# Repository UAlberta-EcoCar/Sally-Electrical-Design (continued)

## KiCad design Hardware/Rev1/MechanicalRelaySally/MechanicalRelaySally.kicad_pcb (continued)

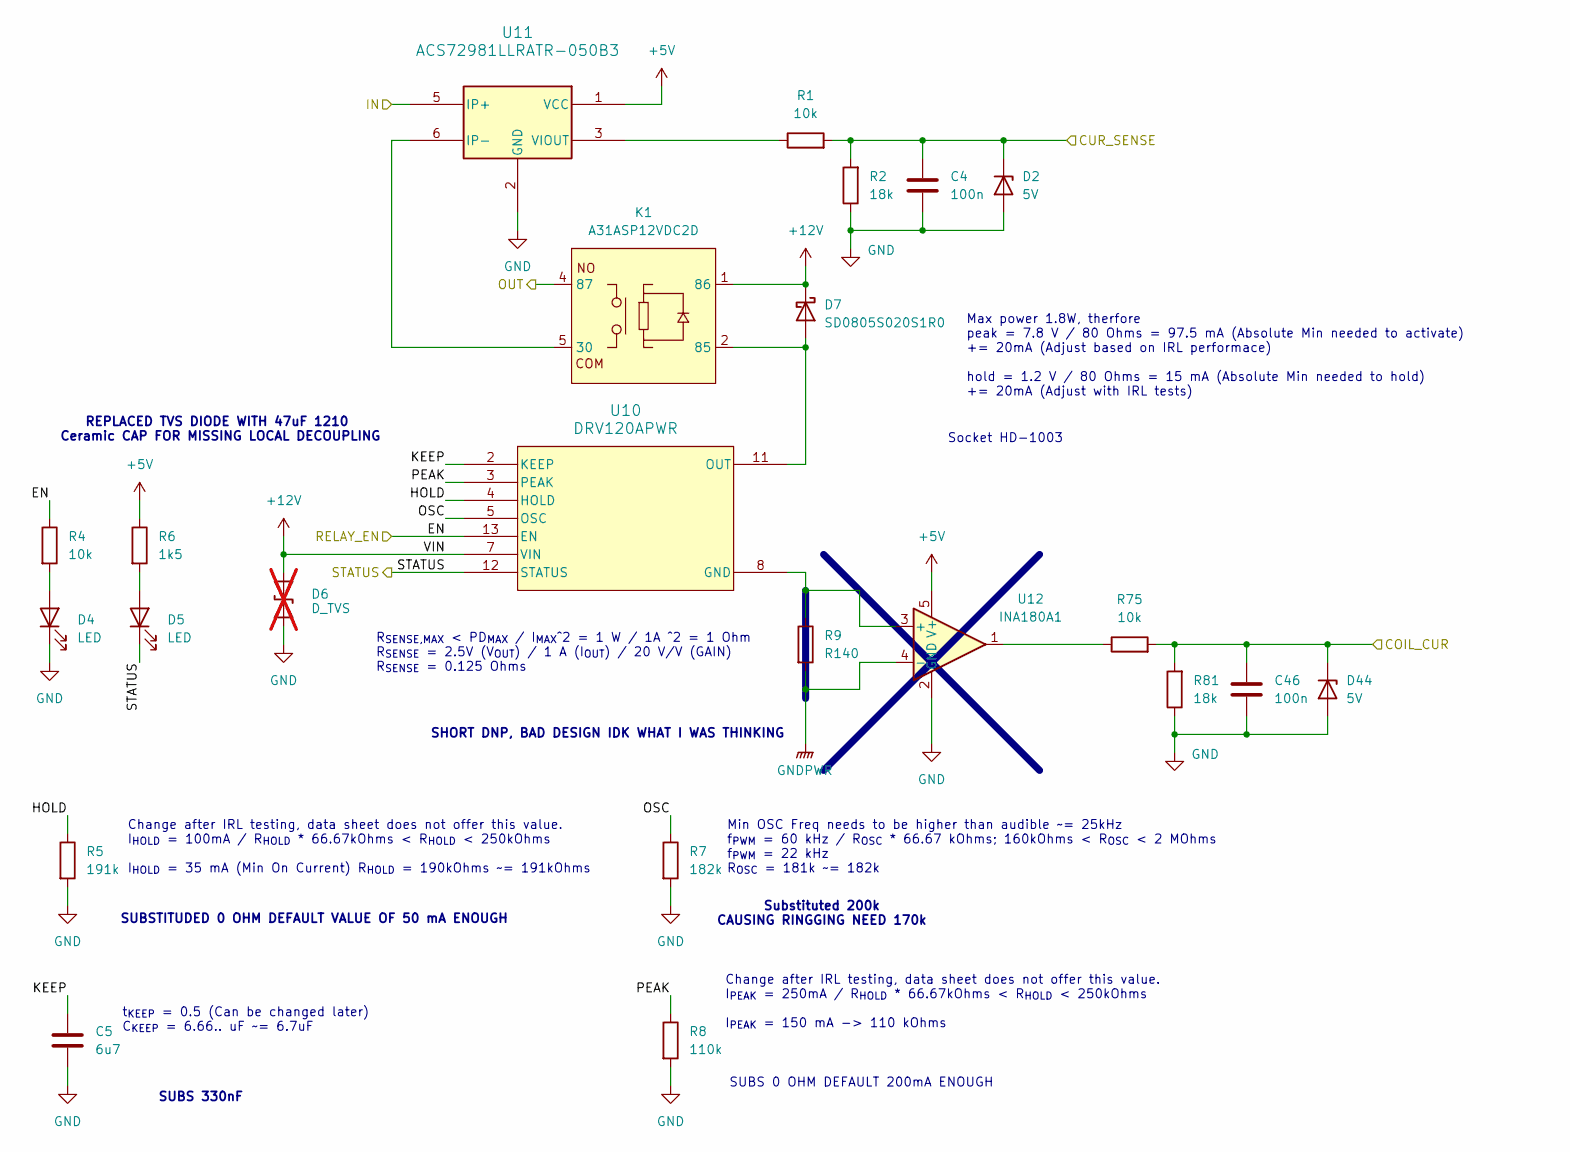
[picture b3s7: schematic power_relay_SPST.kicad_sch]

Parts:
C4, C46: 100n; C_0402_1005Metric
C5: 6u7; C_0603_1608Metric
D2, D44: 5V; D_SOD-323F
D4, D5: LED; LED_0603_1608Metric
D6: D_TVS; D_SOD_123_M; not fitted
D7: SD0805S020S1R0; D_SOD-123; Part# 478-7800-1-ND
K1: A31ASP12VDC2D; A3_HeavyDuty_PCPIN; Part# 2449-A31ASP12VDC2D-ND
R1, R4, R75: 10k; R_0603_1608Metric
R2, R81: 18k; R_0603_1608Metric
R5: 191k; R_0603_1608Metric
R6: 1k5; R_0603_1608Metric
R7: 182k; R_0603_1608Metric
R8: 110k; R_0603_1608Metric
R9: R140; R_1206_3216Metric
U10: DRV120APWR; PW14_TEX
U11: ACS72981LLRATR-050B3; XDCR_ACS72981LLRATR-100B5
U12: INA180A1; SOT-23-5

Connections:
+5V: R6.1, U11.1 (VCC), U12.5 (V+); also elsewhere on the board
+12V: D6.2 (A2), D7.1 (K), K1.1 (86), U10.7 (VIN); also elsewhere on the board
/Microcontroller/MTR_RLY.COIL_CUR: C46.1, D44.1 (K), R75.2, R81.2; also elsewhere on the board
/Microcontroller/MTR_RLY.CUR_SENSE: C4.1, D2.1 (K), R1.2, R2.2; also elsewhere on the board
/Microcontroller/MTR_RLY.RELAY_EN: R4.1, U10.13 (EN); also elsewhere on the board
/Microcontroller/MTR_RLY.STATUS: D5.1 (K), U10.12 (STATUS); also elsewhere on the board
/Power Routing/MOTOR Power Relay1/HOLD: R5.1, U10.4 (HOLD)
/Power Routing/MOTOR Power Relay1/KEEP: C5.1, U10.2 (KEEP)
/Power Routing/MOTOR Power Relay1/OSC: R7.1, U10.5 (OSC)
/Power Routing/MOTOR Power Relay1/PEAK: R8.1, U10.3 (PEAK)
/Power Routing/VOLT_MEAS.FC_OUT: U11.5 (IP+); also elsewhere on the board
/Power Routing/VOLT_MEAS.MTR_OUT: K1.4 (87); also elsewhere on the board
GND: C4.2, C5.2, C46.2, D2.2 (A), D4.1 (K), D6.1 (A1), D44.2 (A), R2.1, R5.2, R7.2, R8.2, R9.2, R81.1, U11.2 (GND), U11.4 (NC), U12.2 (GND), U12.4 (-); also elsewhere on the board
unnamed: D4.2 (A), R4.2
unnamed: D5.2 (A), R6.2
unnamed: D7.2 (A), K1.2 (85), U10.11 (OUT)
unnamed: K1.5 (30), U11.6 (IP-)
unnamed: R75.1, U12.1
unnamed: R9.1, U10.8 (GND), U12.3 (+)
unnamed: R1.1, U11.3 (VIOUT)

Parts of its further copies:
C7: 6u7; C_0603_1608Metric
C10, C50: 100n; C_0402_1005Metric
D8, D47: 5V; D_SOD-323F
D9, D10: LED; LED_0603_1608Metric
D11: D_TVS; D_SOD_123_M; not fitted
D12: SD0805S020S1R0; D_SOD-123; Part# 478-7800-1-ND
K2: A31ASP12VDC2D; A3_HeavyDuty_PCPIN; Part# 2449-A31ASP12VDC2D-ND
R10, R12, R82: 10k; R_0603_1608Metric
R11, R76: 18k; R_0603_1608Metric
R13: 191k; R_0603_1608Metric
R14: 1k5; R_0603_1608Metric
R15: 182k; R_0603_1608Metric
R16: 110k; R_0603_1608Metric
R17: R140; R_1206_3216Metric
U13: DRV120APWR; PW14_TEX
U14: ACS72981LLRATR-050B3; XDCR_ACS72981LLRATR-100B5
U15: INA180A1; SOT-23-5

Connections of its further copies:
+5V: R14.1, U14.1 (VCC), U15.5 (V+); also elsewhere on the board
+12V: D11.2 (A2), D12.1 (K), K2.1 (86), U13.7 (VIN); also elsewhere on the board
/Microcontroller/CAP_RLY.COIL_CUR: C50.1, D47.1 (K), R76.2, R82.2; also elsewhere on the board
/Microcontroller/CAP_RLY.CUR_SENSE: C10.1, D8.1 (K), R10.2, R11.2; also elsewhere on the board
/Microcontroller/CAP_RLY.RELAY_EN: R12.1, U13.13 (EN); also elsewhere on the board
/Microcontroller/CAP_RLY.STATUS: D10.1 (K), U13.12 (STATUS); also elsewhere on the board
/Power Routing/CAP Power Relay/HOLD: R13.1, U13.4 (HOLD)
/Power Routing/CAP Power Relay/KEEP: C7.1, U13.2 (KEEP)
/Power Routing/CAP Power Relay/OSC: R15.1, U13.5 (OSC)
/Power Routing/CAP Power Relay/PEAK: R16.1, U13.3 (PEAK)
/Power Routing/VOLT_MEAS.CAP: U14.5 (IP+); also elsewhere on the board
/Power Routing/VOLT_MEAS.FC_OUT: K2.4 (87); also elsewhere on the board
GND: C7.2, C10.2, C50.2, D8.2 (A), D9.1 (K), D11.1 (A1), D47.2 (A), R11.1, R13.2, R15.2, R16.2, R17.2, R76.1, U14.2 (GND), U15.2 (GND), U15.4 (-); also elsewhere on the board
unnamed: D9.2 (A), R12.2
unnamed: D10.2 (A), R14.2
unnamed: D12.2 (A), K2.2 (85), U13.11 (OUT)
unnamed: K2.5 (30), U14.6 (IP-)
unnamed: R82.1, U15.1
unnamed: R17.1, U13.8 (GND), U15.3 (+)
unnamed: R10.1, U14.3 (VIOUT)

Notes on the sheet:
Change after IRL testing, data sheet does not offer this value. I_{HOLD} = 100mA / R_{HOLD} * 66.67kOhms < R_{HOLD} < 250kOhms I_{HOLD} = 35 mA (Min On Current) R_{HOLD} = 190kOhms ~= 191kOhms
SUBSTITUDED 0 OHM DEFAULT VALUE OF 50 mA ENOUGH
SUBS 330nF
Socket HD-1003
Max power 1.8W, therfore peak = 7.8 V / 80 Ohms = 97.5 mA (Absolute Min needed to activate) += 20mA (Adjust based on IRL performace) hold = 1.2 V / 80 Ohms = 15 mA (Absolute Min needed to hold) += 20mA (Adjust with IRL tests)
Change after IRL testing, data sheet does not offer this value. I_{PEAK} = 250mA / R_{HOLD} * 66.67kOhms < R_{HOLD} < 250kOhms I_{PEAK} = 150 mA -> 110 kOhms
REPLACED TVS DIODE WITH 47uF 1210 Ceramic CAP FOR MISSING LOCAL DECOUPLING
Substituted 200k CAUSING RINGGING NEED 170k
Min OSC Freq needs to be higher than audible ~= 25kHz f_{PWM} = 60 kHz / R_{OSC} * 66.67 kOhms; 160kOhms < R_{OSC} < 2 MOhms f_{PWM} = 22 kHz R_{OSC} = 181k ~= 182k
SUBS 0 OHM DEFAULT 200mA ENOUGH
R_{SENSE,MAX} < PD_{MAX} / I_{MAX}^2 = 1 W / 1A ^2 = 1 Ohm R_{SENSE} = 2.5V (V_{OUT}) / 1 A (I_{OUT}) / 20 V/V (GAIN) R_{SENSE} = 0.125 Ohms
SHORT DNP, BAD DESIGN IDK WHAT I WAS THINKING
t_{KEEP} = 0.5 (Can be changed later) C_{KEEP} = 6.66.. uF ~= 6.7uF

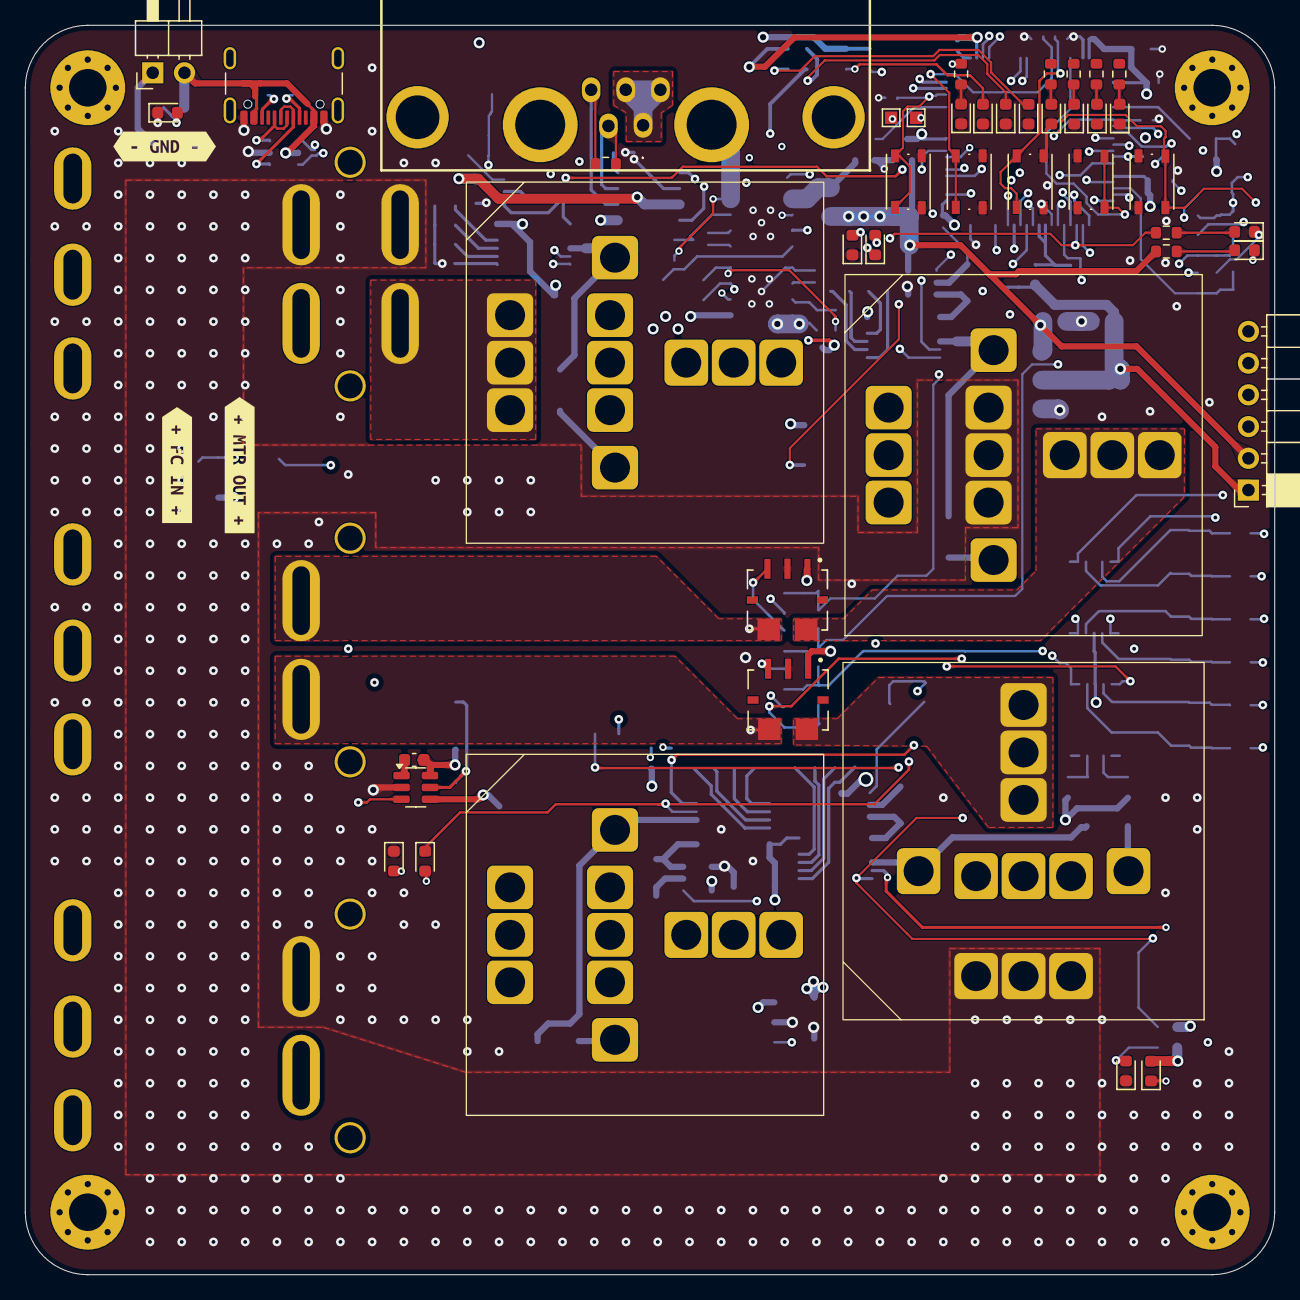
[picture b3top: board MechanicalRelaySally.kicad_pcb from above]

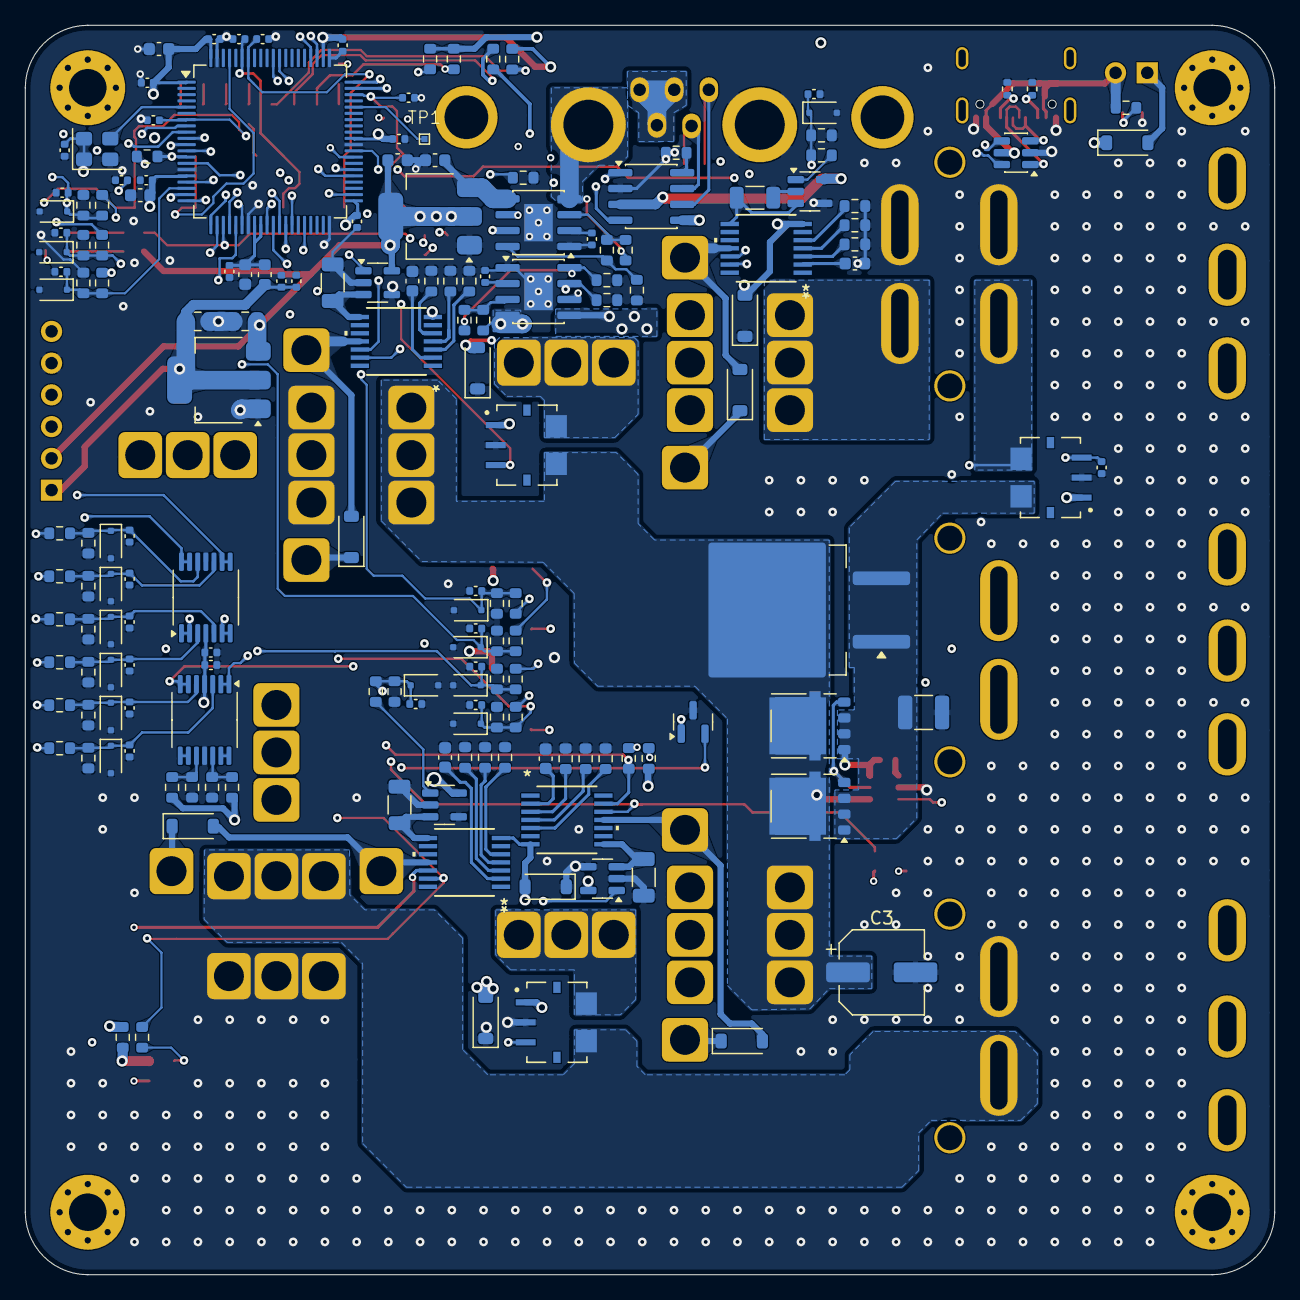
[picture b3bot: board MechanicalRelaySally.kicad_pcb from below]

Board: 4 copper layers, 100.0 x 100.0 mm, 224 parts (170 on the bottom side), 138 nets.

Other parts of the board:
kibuzzard-697D9F6C: G***; kibuzzard-697D9F6C
kibuzzard-697D96F8: G***; kibuzzard-697D96F8
kibuzzard-697D96FE: G***; kibuzzard-697D96FE

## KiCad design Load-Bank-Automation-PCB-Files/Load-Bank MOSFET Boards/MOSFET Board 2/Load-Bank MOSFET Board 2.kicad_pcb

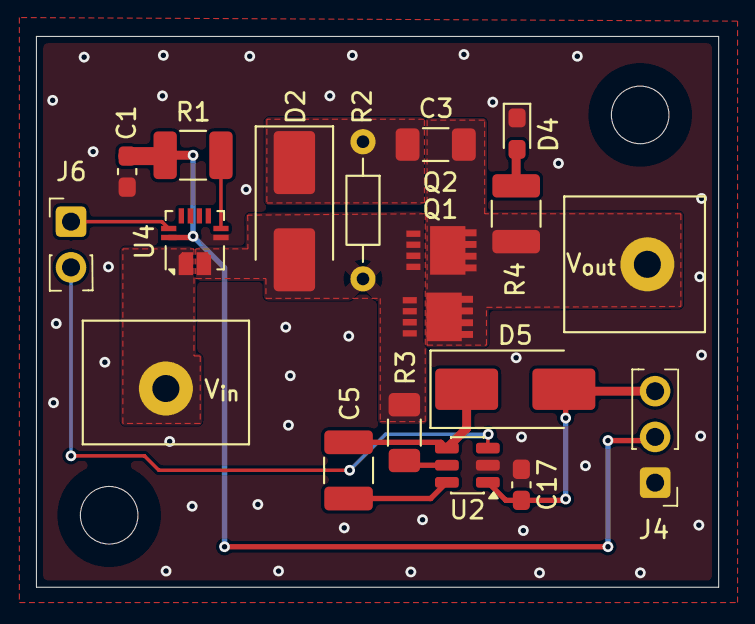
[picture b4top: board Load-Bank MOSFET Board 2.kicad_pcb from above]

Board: 2 copper layers, 37.9 x 30.6 mm, 21 parts (0 on the bottom side), 14 nets.

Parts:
C1, C17: 100n; C_0603_1608Metric_Pad1.08x0.95mm_HandSolder
C3: 68n; C_1206_3216Metric_Pad1.33x1.80mm_HandSolder
C5: 4u7; C_1210_3225Metric_Pad1.33x2.70mm_HandSolder
D2, D5: SBR1U200P1; D_SMB_Handsoldering
D4: LED; LED_0603_1608Metric_Pad1.05x0.95mm_HandSolder
H1, H3: MountingHole; MountingHole_3.2mm_M3
J4: Conn_01x03; IDC-Header_1x03_P2.54mm_Vertical
J6: Conn_01x02; IDC-Header_1x02_P2.54mm_Vertical
Q1, Q2: GSGN0648; PPAK 3x3
R1: 10k; R_1210_3225Metric_Pad1.30x2.65mm_HandSolder
R2: 13k; R_Axial_DIN0204_L3.6mm_D1.6mm_P7.62mm_Horizontal
R3: 39; R_1206_3216Metric_Pad1.30x1.75mm_HandSolder
R4: 20k; R_1210_3225Metric_Pad1.30x2.65mm_HandSolder
U2: IRS10752LTRPBF; SOT-23-6
U4: ACS711xEXLT-31AB; Allegro_QFN-12-10-1EP_3x3mm_P0.5mm
V_{in}: MountingHole; TerminalBlock_MetzConnect_360271_1x01_Horizontal_ScrewM3.0_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
V_{out}: MountingHole; TerminalBlock_MetzConnect_360271_1x01_Horizontal_ScrewM3.0_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

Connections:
+3V3: C1.2, J4.2, R1.2, U4.10 (VCC)
+12V: C17.2, D5.2 (A), J4.3, U2.1 (V_{cc})
/MOSFET Board 2/Current_ADC: J6.1, U4.9 (VIOUT)
/MOSFET Board 2/PWM: J6.2, U2.3 (IN)
/MOSFET Board 2/V_{IN}: U4.1 (IP+), V_{in}.1
/MOSFET Board 2/V_{OUT}: C3.1, Q1.3 (S), Q2.3 (S), R4.1, V_{out}.1
GND: C1.1, C17.1, D4.1 (K), J4.1, U2.2 (COM), U4.3 (GND)
unnamed: D2.2 (A), Q1.1 (D), Q1.2 (G), Q2.1 (D), Q2.2 (G), R2.2, R3.1, U4.2 (IP-)
unnamed: C3.2, D2.1 (K), R2.1
unnamed: D4.2 (A), R4.2
unnamed: C5.1, D5.1 (K), U2.4 (V_{B})
unnamed: R3.2, U2.5 (HO)
unnamed: C5.2, U2.6 (V_{s})
unnamed: R1.1, U4.4 (~FAULT)

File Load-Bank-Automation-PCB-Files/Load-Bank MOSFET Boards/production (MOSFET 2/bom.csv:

Designator,Footprint,Quantity,Value,LCSC Part #
"C1, C17",0603,2,100n,
C3,1206,1,68n,
C5,1210,1,4u7,
"D2, D5",D_SMB_Handsoldering,2,SBR1U200P1,
D4,0603,1,LED,
J4,IDC-Header_1x03_P2.54mm_Vertical,1,Conn_01x03,
J6,IDC-Header_1x02_P2.54mm_Vertical,1,Conn_01x02,
"Q1, Q2",PPAK 3x3,2,GSGN0648,
R1,1210,1,10k,
R2,R_Axial_DIN0204_L3.6mm_D1.6mm_P7.62mm_Horizontal,1,13k,
R3,1206,1,39,
R4,1210,1,20k,
U2,SOT-23-6,1,IRS10752LTRPBF,
U4,Allegro_QFN-12-10-1EP_3x3mm_P0.5mm,1,ACS711xEXLT-31AB,

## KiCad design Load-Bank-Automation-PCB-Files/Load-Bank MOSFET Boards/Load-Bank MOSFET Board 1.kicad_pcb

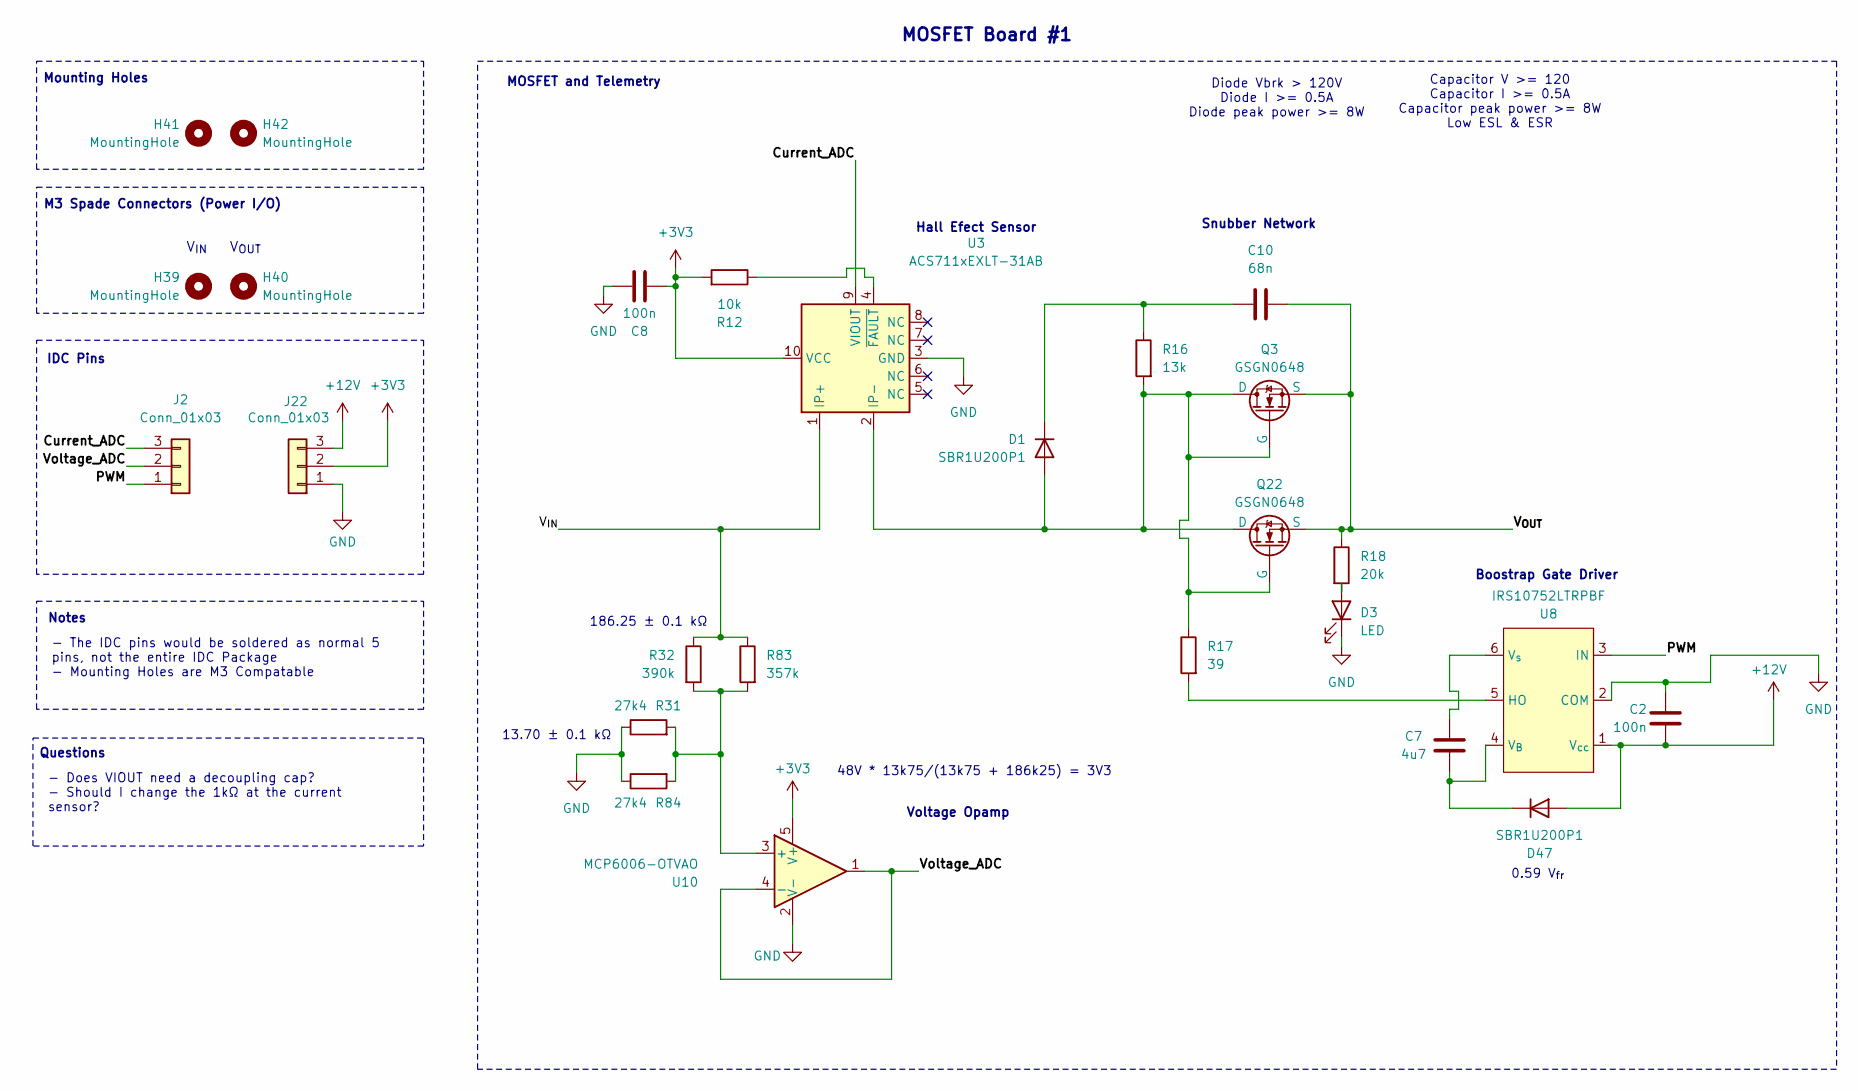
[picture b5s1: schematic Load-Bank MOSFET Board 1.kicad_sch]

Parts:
C2, C8: 100n; C_0603_1608Metric_Pad1.08x0.95mm_HandSolder
C7: 4u7; C_1210_3225Metric_Pad1.33x2.70mm_HandSolder
C10: 68n; C_1206_3216Metric_Pad1.33x1.80mm_HandSolder
D1, D47: SBR1U200P1; D_SMB_Handsoldering
D3: LED; LED_0603_1608Metric_Pad1.05x0.95mm_HandSolder
H39, H40: MountingHole; TerminalBlock_MetzConnect_360271_1x01_Horizontal_ScrewM3.0_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
H41, H42: MountingHole; MountingHole_3.2mm_M3
J2, J22: Conn_01x03; IDC-Header_1x03_P2.54mm_Vertical
Q3, Q22: GSGN0648; PPAK 3x3
R12: 10k; R_1210_3225Metric_Pad1.30x2.65mm_HandSolder
R16: 13k; R_Axial_DIN0204_L3.6mm_D1.6mm_P7.62mm_Horizontal
R17: 39; R_1206_3216Metric_Pad1.30x1.75mm_HandSolder
R18: 20k; R_1210_3225Metric_Pad1.30x2.65mm_HandSolder
R31, R84: 27k4; R_1206_3216Metric_Pad1.30x1.75mm_HandSolder
R32: 390k; R_1206_3216Metric_Pad1.30x1.75mm_HandSolder
R83: 357k; R_1206_3216Metric_Pad1.30x1.75mm_HandSolder
U3: ACS711xEXLT-31AB; Allegro_QFN-12-10-1EP_3x3mm_P0.5mm
U8: IRS10752LTRPBF; SOT-23-6
U10: MCP6006-OTVAO; SOT-23-5

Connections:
+3V3: C8.2, J22.2, R12.2, U3.10 (VCC), U10.5 (V+)
+12V: C2.2, D47.2 (A), J22.3, U8.1 (V_{cc})
/Mosfet Board 1/Current_ADC: J2.3, U3.9 (VIOUT)
/Mosfet Board 1/PWM: J2.1, U8.3 (IN)
/Mosfet Board 1/V_{IN}: H39.1, R32.1, R83.1, U3.1 (IP+)
/Mosfet Board 1/V_{OUT}: C10.1, H40.1, Q3.3 (S), Q22.3 (S), R18.1
/Mosfet Board 1/Voltage_ADC: J2.2, U10.1, U10.4 (-)
GND: C2.1, C8.1, D3.1 (K), J22.1, R31.1, R84.1, U3.3 (GND), U8.2 (COM), U10.2 (V-)
unnamed: D1.2 (A), Q3.1 (D), Q3.2 (G), Q22.1 (D), Q22.2 (G), R16.2, R17.1, U3.2 (IP-)
unnamed: C10.2, D1.1 (K), R16.1
unnamed: D3.2 (A), R18.2
unnamed: C7.1, D47.1 (K), U8.4 (V_{B})
unnamed: R12.1, U3.4 (~FAULT)
unnamed: R17.2, U8.5 (HO)
unnamed: C7.2, U8.6 (V_{s})
unnamed: R31.2, R32.2, R83.2, R84.2, U10.3 (+)

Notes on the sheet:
IDC Pins
Boostrap Gate Driver
186.25 ± 0.1 kΩ
Capacitor V >= 120 Capacitor I >= 0.5A Capacitor peak power >= 8W Low ESL & ESR
Mounting Holes
MOSFET and Telemetry
0.59 V_{fr}
V_{OUT}
V_{IN}
M3 Spade Connectors (Power I/O)
48V * 13k75/(13k75 + 186k25) = 3V3
Hall Efect Sensor
Voltage Opamp
- The IDC pins would be soldered as normal 5 pins, not the entire IDC Package - Mounting Holes are M3 Compatable
Diode Vbrk > 120V Diode I >= 0.5A Diode peak power >= 8W
Snubber Network
Questions
13.70 ± 0.1 kΩ
- Does VIOUT need a decoupling cap? - Should I change the 1kΩ at the current sensor?
MOSFET Board #1
Notes

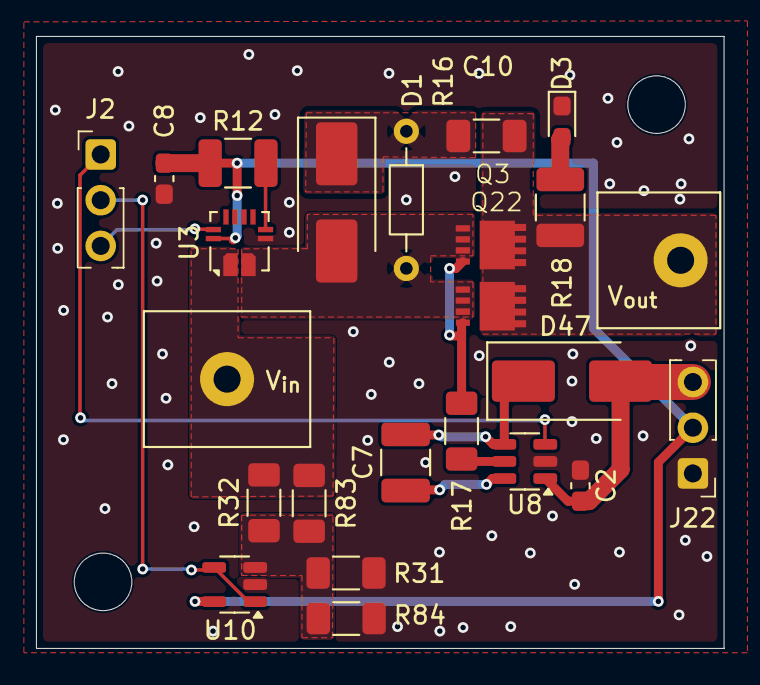
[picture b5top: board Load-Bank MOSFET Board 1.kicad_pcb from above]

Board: 2 copper layers, 38.2 x 34.0 mm, 26 parts (0 on the bottom side), 16 nets.

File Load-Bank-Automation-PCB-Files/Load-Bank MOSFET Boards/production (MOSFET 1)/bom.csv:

Designator,Footprint,Quantity,Value,LCSC Part #
C10,1206,1,68n,
"C2, C8",0603,2,100n,
C7,1210,1,4.7u,
"D1, D47",D_SMB_Handsoldering,2,SBR1U200P1,
D3,0603,1,LED,
"J2, J22",IDC_PinHeader_1x03_P1.00mm_Vertical,2,Conn_01x03,
"Q22, Q3",Goodarksemiconductor_PPAK_3x3,2,GSGN0648,
R12,1210,1,10k,
R16,R_Axial_DIN0204_L3.6mm_D1.6mm_P7.62mm_Horizontal,1,13k,
R17,1206,1,39,
R18,1210,1,20k,
"R31, R84",1206,2,27k4,
R32,1206,1,390k,
R83,1206,1,357k,
U10,SOT-23-5,1,MCP6006-OTVAO,
U3,Allegro_QFN-12-10-1EP_3x3mm_P0.5mm,1,ACS711xEXLT-31AB,
U8,SOT-23-6,1,IRS10752LTRPBF,

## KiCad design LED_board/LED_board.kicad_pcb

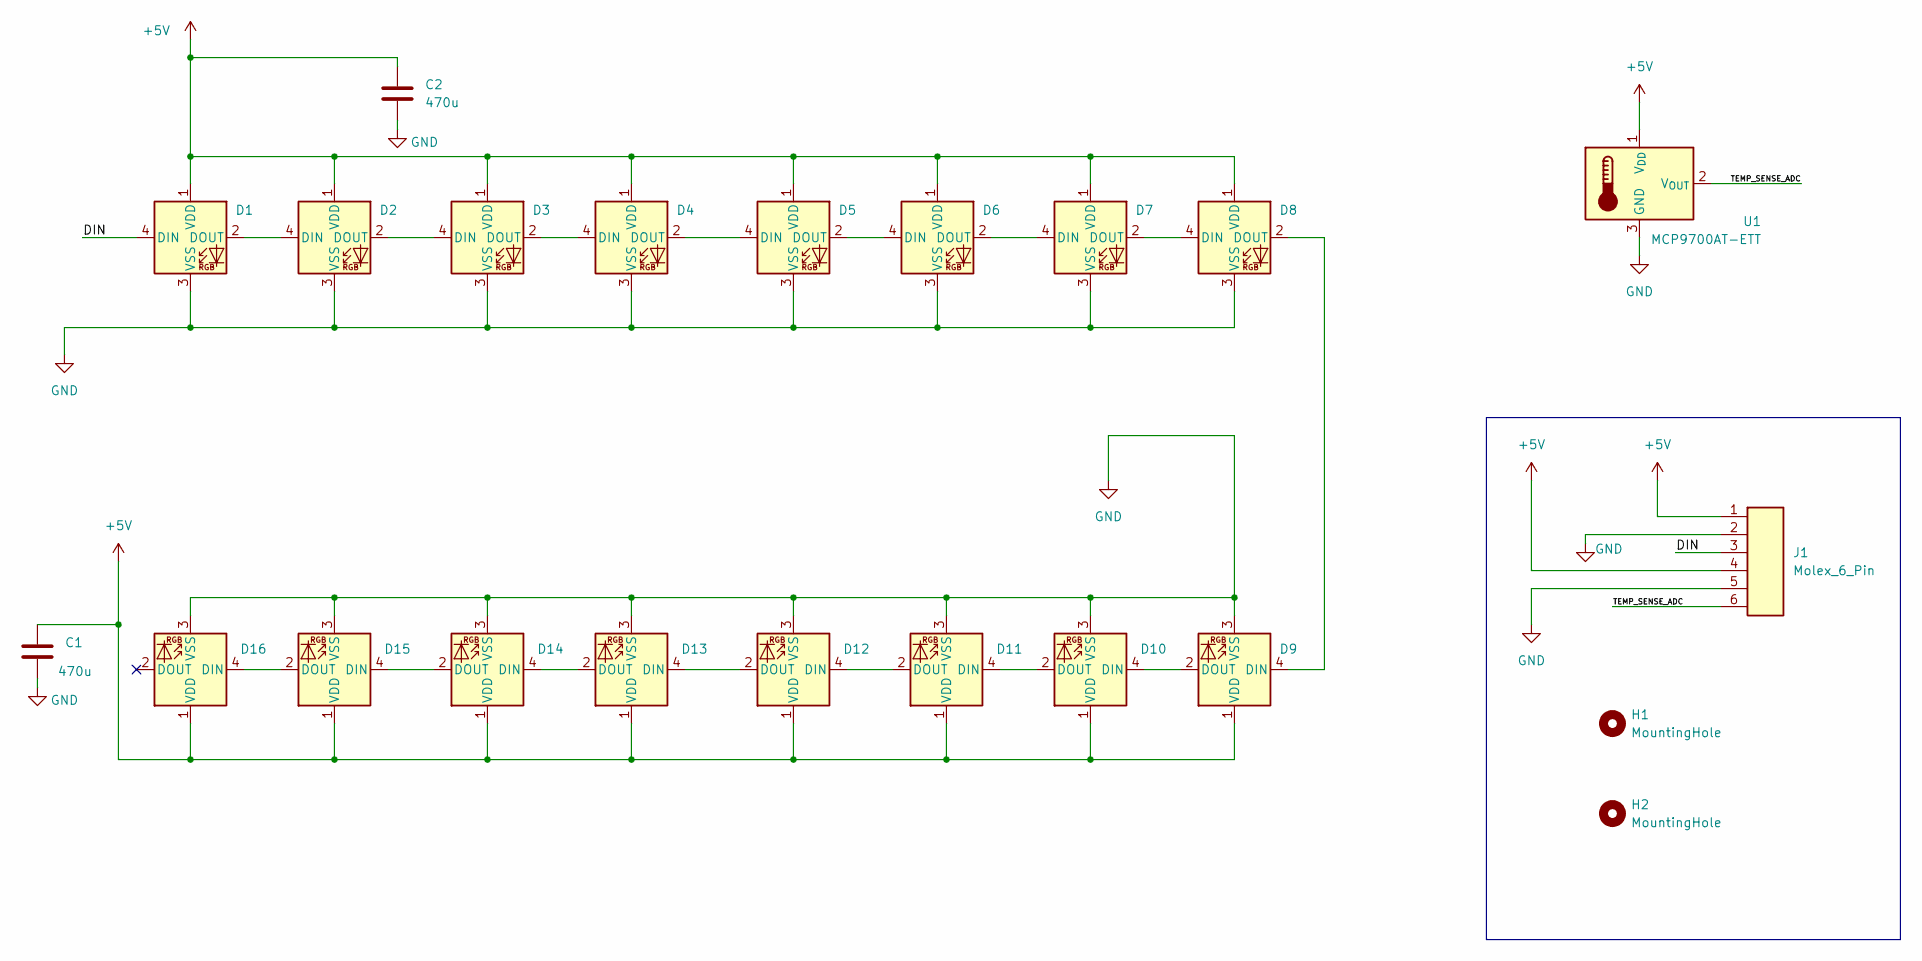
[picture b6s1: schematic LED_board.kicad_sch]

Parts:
C1, C2: 470u; C_0603_1608Metric
D1, D2, D3, D4, D5, D6, D7, D8, D9, D10, D11, D12, D13, D14, D15, D16: WS2812B; LED_WS2812B_PLCC4_5.0x5.0mm_P3.2mm
H1, H2: MountingHole; MountingHole_3mm
J1: Molex_6_Pin; CONN_SD-43045-004_06_MOL
U1: MCP9700AT-ETT; SOT-23; LCSC# C42288

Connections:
+5V: C1.1, C2.1, D1.1 (VDD), D2.1 (VDD), D3.1 (VDD), D4.1 (VDD), D5.1 (VDD), D6.1 (VDD), D7.1 (VDD), D8.1 (VDD), D9.1 (VDD), D10.1 (VDD), D11.1 (VDD), D12.1 (VDD), D13.1 (VDD), D14.1 (VDD), D15.1 (VDD), D16.1 (VDD), J1.1, J1.4, U1.1 (V_{DD})
/DIN: D1.4 (DIN), J1.3
/TEMP_SENSE_ADC: J1.6, U1.2 (V_{OUT})
GND: C1.2, C2.2, D1.3 (VSS), D2.3 (VSS), D3.3 (VSS), D4.3 (VSS), D5.3 (VSS), D6.3 (VSS), D7.3 (VSS), D8.3 (VSS), D9.3 (VSS), D10.3 (VSS), D11.3 (VSS), D12.3 (VSS), D13.3 (VSS), D14.3 (VSS), D15.3 (VSS), D16.3 (VSS), J1.2, J1.5, U1.3 (GND)
unnamed: D1.2 (DOUT), D2.4 (DIN)
unnamed: D2.2 (DOUT), D3.4 (DIN)
unnamed: D3.2 (DOUT), D4.4 (DIN)
unnamed: D4.2 (DOUT), D5.4 (DIN)
unnamed: D5.2 (DOUT), D6.4 (DIN)
unnamed: D6.2 (DOUT), D7.4 (DIN)
unnamed: D7.2 (DOUT), D8.4 (DIN)
unnamed: D8.2 (DOUT), D9.4 (DIN)
unnamed: D9.2 (DOUT), D10.4 (DIN)
unnamed: D10.2 (DOUT), D11.4 (DIN)
unnamed: D11.2 (DOUT), D12.4 (DIN)
unnamed: D12.2 (DOUT), D13.4 (DIN)
unnamed: D13.2 (DOUT), D14.4 (DIN)
unnamed: D14.2 (DOUT), D15.4 (DIN)
unnamed: D15.2 (DOUT), D16.4 (DIN)

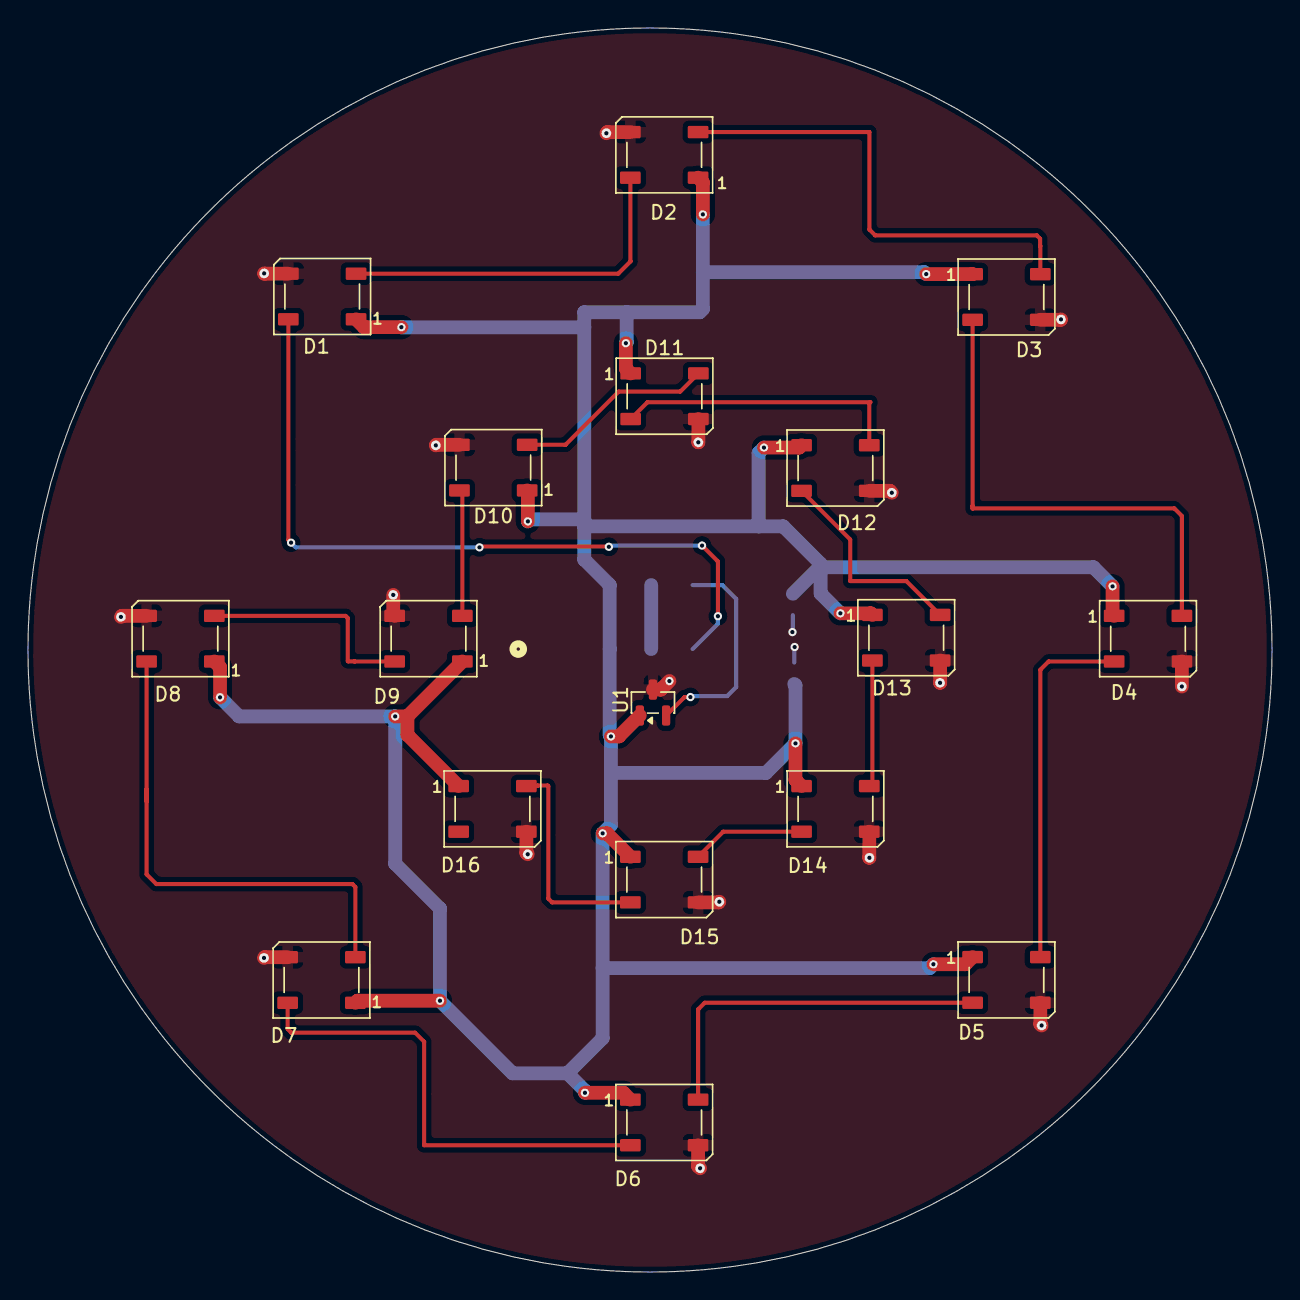
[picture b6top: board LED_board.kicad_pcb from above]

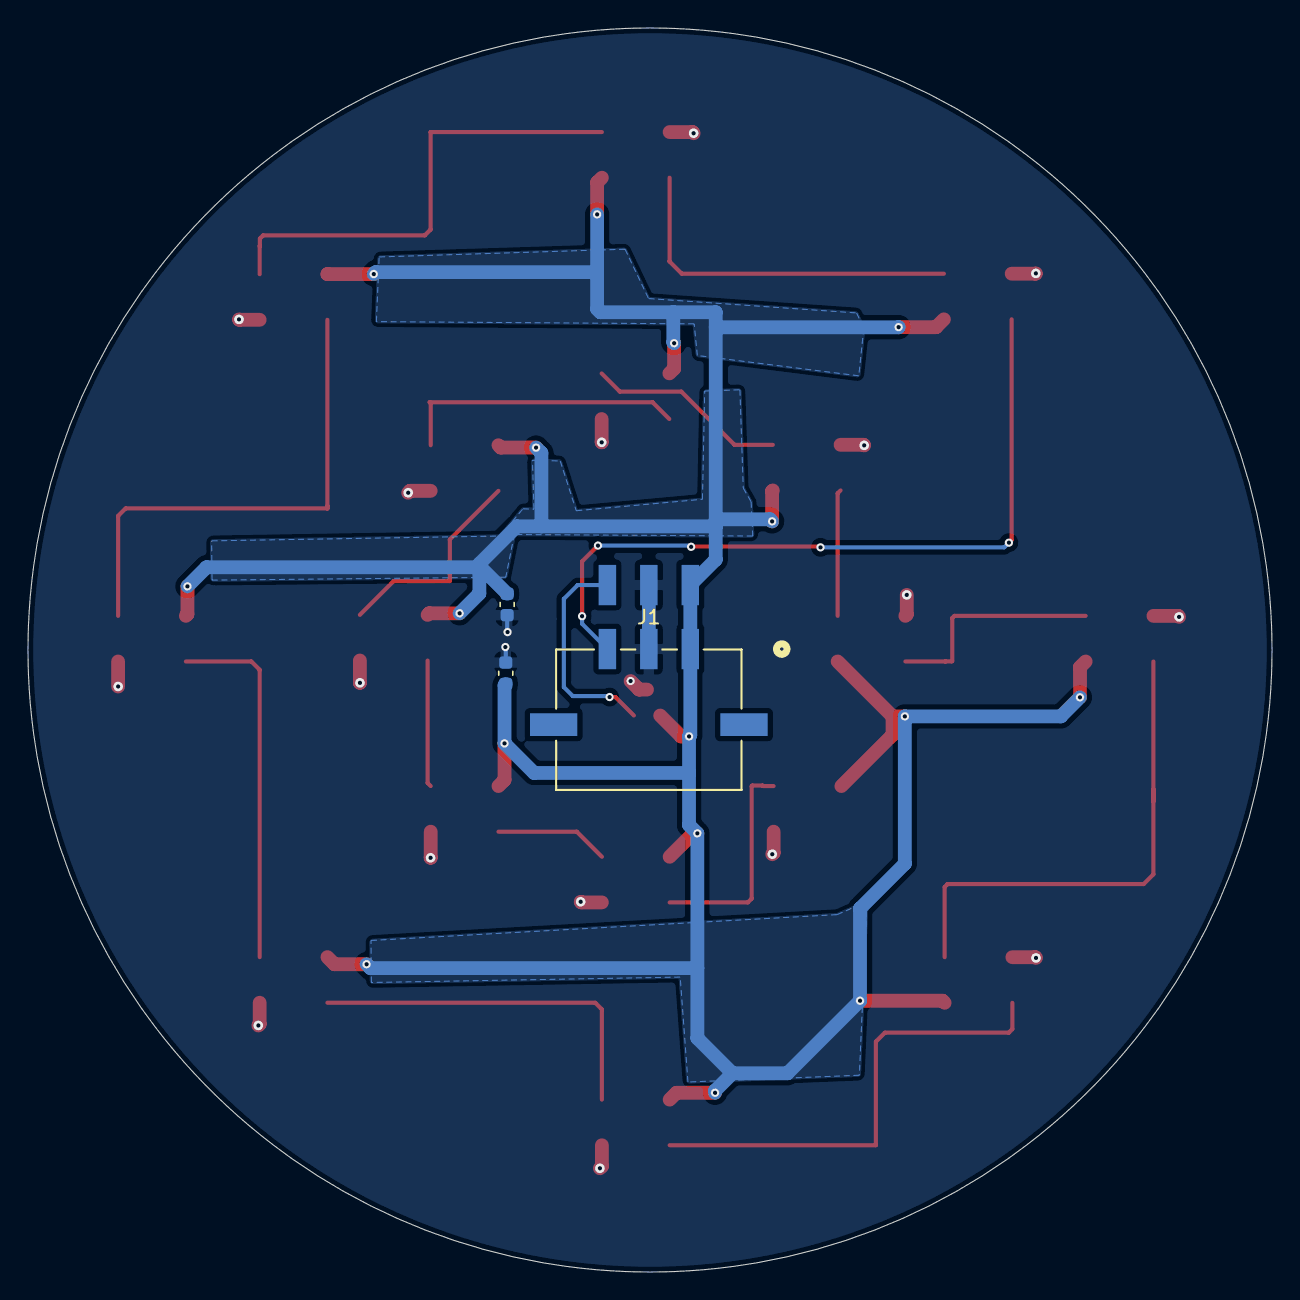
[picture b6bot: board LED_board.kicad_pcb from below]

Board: 2 copper layers, 90.0 x 90.0 mm, 22 parts (3 on the bottom side), 19 nets.
